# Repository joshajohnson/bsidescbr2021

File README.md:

# BSidesCBR2021
Slides and Design Files for BSides Canberra 2021

## Contents:
- `slides-ehd` slides for my "Electronic Hardware Design" talk.
- `pcb-ehd` design files for my "Electronic Hardware Design" talk.
    - `pcb-ehd/integrated-pcb` is the fully integrated bow tie.
    - `pcb-ehd/module-pcb` is the circular PCB using a Feather and microphone breakout.
    - `pcb-ehd/parts-lib` are custom footprints used in the above projects.
- `pcb-sao-magpie` design files for the Magpie SAO.

## PCB Design Files
**NOTE:** Both of the `pcb-ehd` projects have major issues with footprints and layout. **DO NOT manufacture these designs.** The Magpie SAO can however be manufactured if desired.

The `pcb-ehd` files require a recent KiCad Nightly build to open, whereas the SAO can be opened in KiCad 5.

In each of the project folders, you will find the below files:

- `proj.kicad_pro` is the overall KiCad project (`.pro` for V5).
- `proj.kicad_sch` is the schematic (`.sch` for V5).
- `proj.kicad_pcb` is the physical layout.
- `outputs/schematic.pdf` is a PDF of the schematic.
- `outputs/assembly.html` is a "Human Pick and Place" file which will help you hand assemble the board.
- `outputs/bom.csv` is the bill of materials required to populate the boards. I have not fully specified the resistors and capacitors for the integrated PCB.

## Resources:   
- [Digikey KiCad Series](https://www.youtube.com/watch?v=vaCVh2SAZY4)
- [KiCad PCB Design Walkthrough](https://www.youtube.com/watch?v=C7-8nUU6e3E)
- [PCB Design in Reverse](https://www.youtube.com/watch?v=CV68US8gZMk)
- [PCB Design Tutorial](https://alternatezone.com/electronics/files/-PCBDesignTutorialRevA.pdf)
- [Chris Gammell / Contextual Electronics](https://www.youtube.com/user/-contextualelectronic/videos)
- [100 Hardware Design Tips](https://www.youtube.com/watch?v=ZpMvKJzZk90&-list=PLXvLToQzgzddPKq_txEXNe0pxaSHqPtMO)
- [PCB Art](http://www.andrewsowa.com/blog/2017/3/19/creating-the-benchoff-nickel) 
- [Interactive HTML BOM](https://github.com/openscopeproject/InteractiveHtmlBom)

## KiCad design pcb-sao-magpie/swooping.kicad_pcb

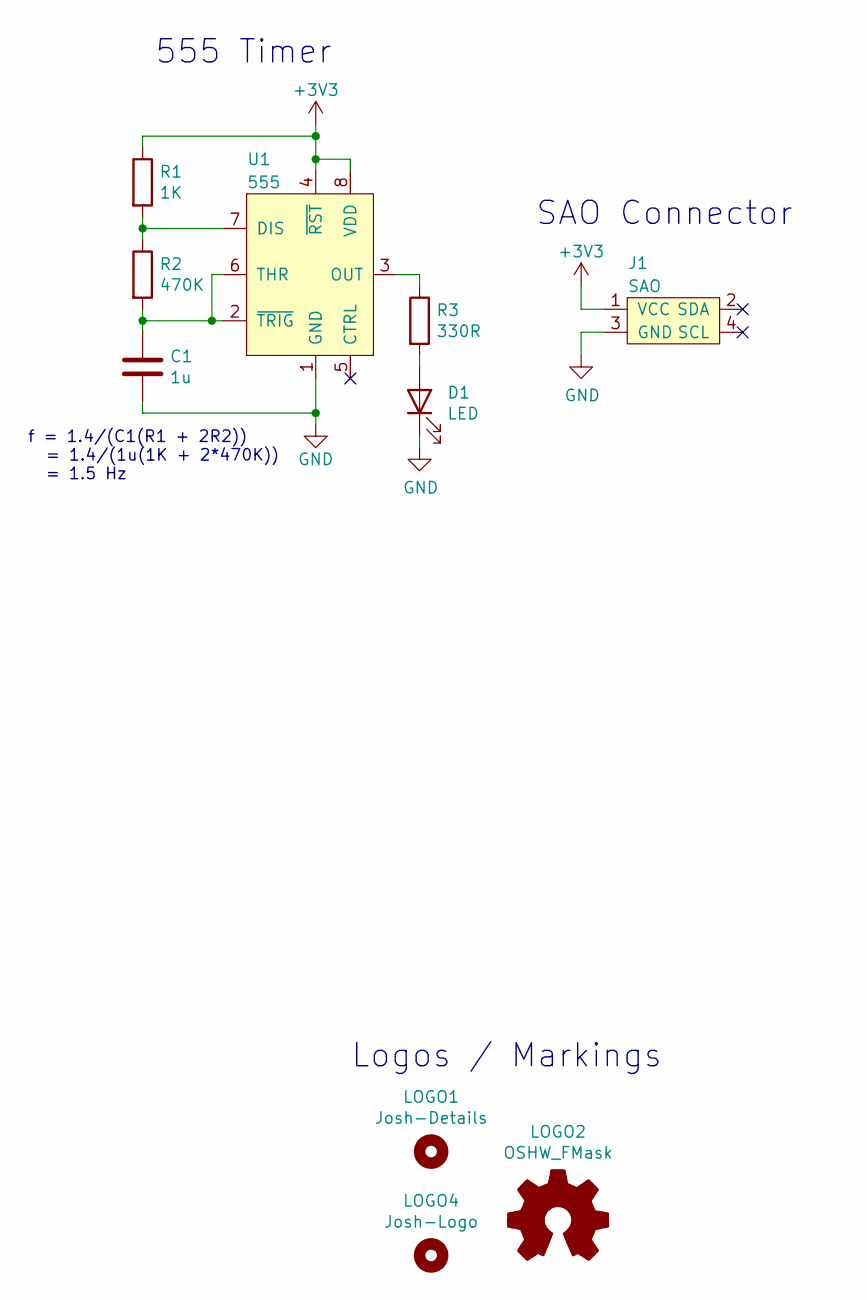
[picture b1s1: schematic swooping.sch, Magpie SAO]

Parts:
C1: 1u; C_1206_3216Metric_Pad1.42x1.75mm_HandSolder; MPN CL31B105KOFNNNE
D1: LED; LED_D5.0mm; MPN L513SRD-C
J1: SAO; PinHeader_2x02_P2.54mm_Vertical; MPN 10129382-904001BLF
LOGO1: Josh-Details; josh-details
LOGO2: OSHW_FMask; OSHW_Logo_3.6x3.6_F.Mask
LOGO4: Josh-Logo; josh-johnson-logo-8_6x1_5
R1: 1K; R_1206_3216Metric_Pad1.42x1.75mm_HandSolder; MPN RMCF1206JT1K00
R2: 470K; R_1206_3216Metric_Pad1.42x1.75mm_HandSolder; MPN RMCF1206JT470K
R3: 330R; R_1206_3216Metric_Pad1.42x1.75mm_HandSolder; MPN RMCF1206JT330R
U1: 555; SOIC-8_3.9x4.9mm_P1.27mm; MPN TLC555

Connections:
+3V3: J1.1 (VCC), R1.1, U1.4 (~RST), U1.8 (VDD)
GND: C1.2, D1.1 (K), J1.3 (GND), U1.1 (GND)
unnamed: C1.1, R2.2, U1.2 (~TRIG), U1.6 (THR)
unnamed: D1.2 (A), R3.2
unnamed: R1.2, R2.1, U1.7 (DIS)
unnamed: R3.1, U1.3 (OUT)

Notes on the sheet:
555 Timer
f = 1.4/(C1(R1 + 2R2)) = 1.4/(1u(1K + 2*470K)) = 1.5 Hz
SAO Connector
Logos / Markings

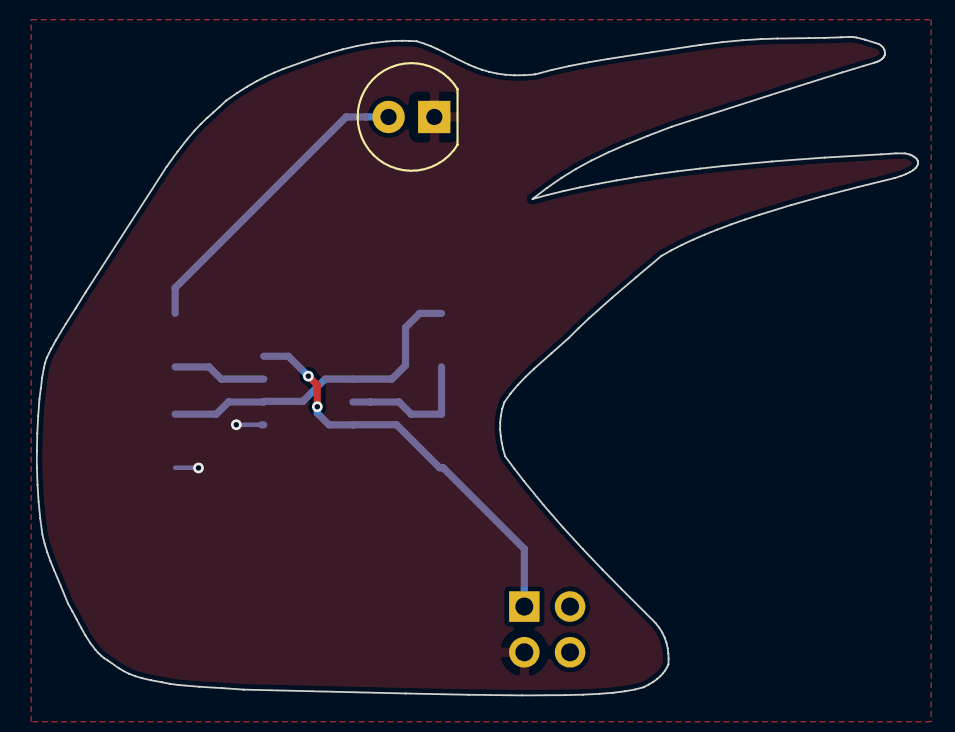
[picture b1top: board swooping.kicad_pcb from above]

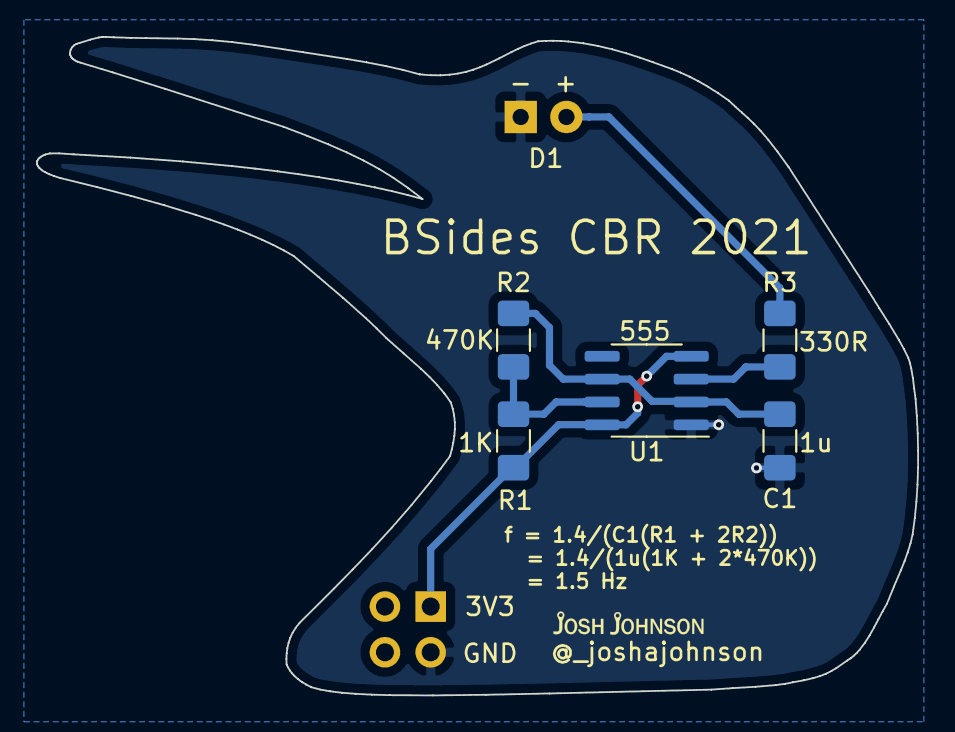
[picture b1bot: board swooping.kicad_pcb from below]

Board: 2 copper layers, 49.0 x 36.6 mm, 10 parts (8 on the bottom side), 6 nets.

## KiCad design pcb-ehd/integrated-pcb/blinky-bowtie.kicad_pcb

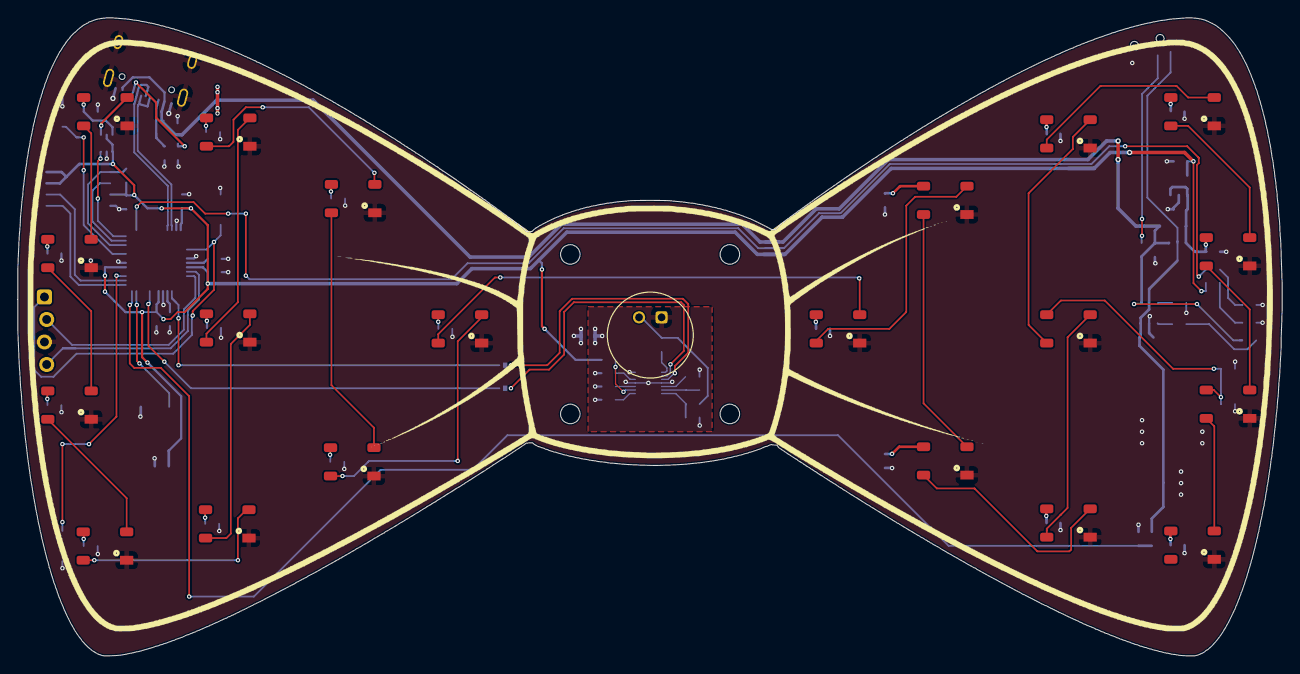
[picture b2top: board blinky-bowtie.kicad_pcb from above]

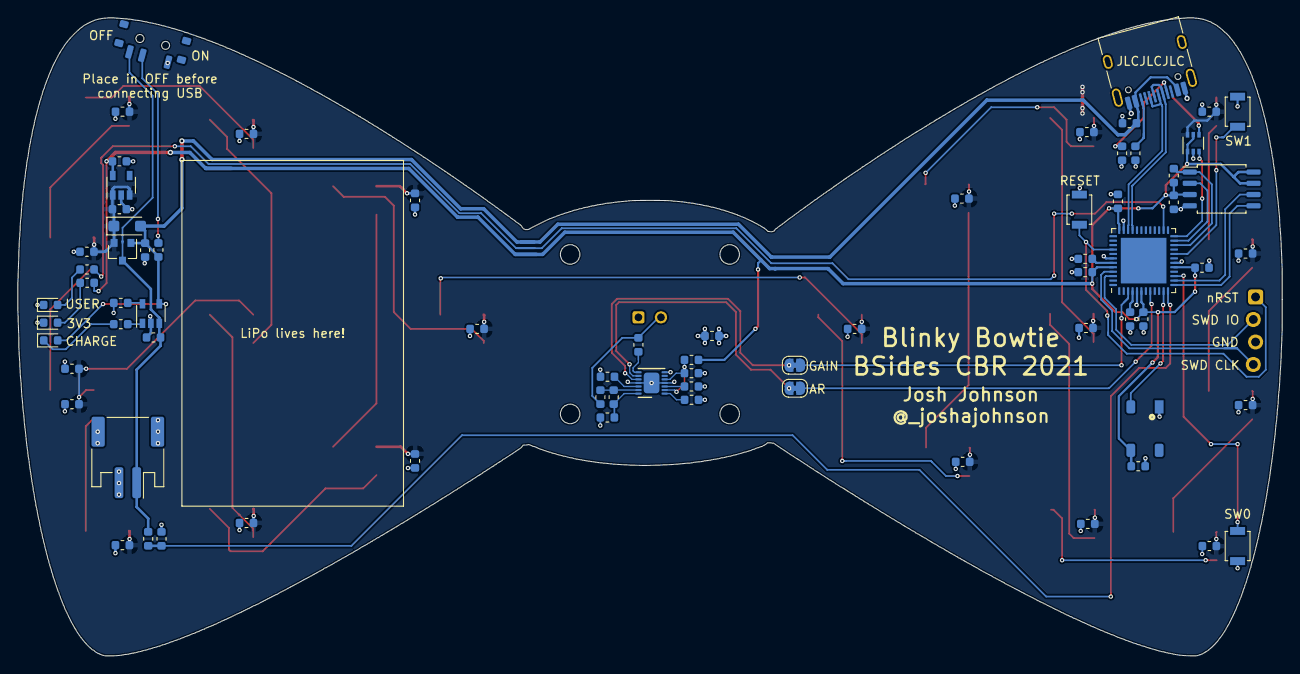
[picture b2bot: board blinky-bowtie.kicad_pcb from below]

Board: 2 copper layers, 142.7 x 72.0 mm, 101 parts (74 on the bottom side), 63 nets.

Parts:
C1: 4u7; C_0603_1608Metric
C2, C5, C7, C8, C9, C10, C12, C13, C14, C15, C16, C17, C18, C22, C23, C24, C25, C26, C27, C28, C29, C30, C31, C32, C33, C36: 100n; C_0603_1608Metric
C3, C4, C6: 10u; C_0603_1608Metric
C11, C19, C20, C21, C37: 1u; C_0603_1608Metric
C34: 470n; C_0603_1608Metric
C35: 2u2; C_0603_1608Metric
D1: RED; LED_0603_1608Metric
D2: ORG; LED_0603_1608Metric
D3, D6, D7, D8, D9, D10, D11, D12, D13, D14, D15, D16, D17, D18, D19, D20, D21, D22, D23, D24, D25: WS2812B; LED_WS2812B_PLCC4_5.0x5.0mm_P3.2mm
D4: PWR; LED_0603_1608Metric
D5: MBR120; D_SOD-123FL
FB1, FB2: 600R; R_0603_1608Metric
H1, H2, H3, H4: M2; MountingHole_2.2mm_M2_DIN965
J1: USB_C_Receptacle_USB2.0; USB_C_Receptacle_HRO_TYPE-C-31-M-12
J2: JST_PH; JST_PH_S2B-PH-SM4-TB_1x02-1MP_P2.00mm_Horizontal
J3: SWD; 4_PIN_THT_Staggered
JP1: GAIN; SolderJumper-2_P1.3mm_Bridged_RoundedPad1.0x1.5mm
JP2: AR; SolderJumper-2_P1.3mm_Bridged_RoundedPad1.0x1.5mm
LOGO1: F.Silk; bowtie-f-silk
LOGO2: Edge.Cuts; bowtie-edge-cuts
MK1: Mic; MIC_CMA-4544PF-W
Q1: DMP2045U; SOT-23
R1, R2, R7: 1K; R_0603_1608Metric
R3, R5: 5K1; R_0603_1608Metric
R4, R6, R8, R10: 100K; R_0603_1608Metric
R9, R13, R14: 10K; R_0603_1608Metric
R11: 150K; R_0603_1608Metric
R12: 2K2; R_0603_1608Metric
SW1, SW2, SW3: B3U; SW_SPST_B3U-1000P
SW4: SLIDE; SW_SPDT_PCM12
U1: MCP73831T-2; SOT-23-5
U2: ATSAMD21G18A-M; QFN-48-1EP_7x7mm_P0.5mm_EP5.15x5.15mm
U3: AP2112K-3.3; SOT-23-5
U4: MAX9814; DFN-14-1EP_3x3mm_P0.4mm_EP1.78x2.35mm
U5: W25Q32JVZPIQ; SOP-8_5.28x5.23mm_P1.27mm
U6: SN74LVC1T45DCK; SOT-363_SC-70-6

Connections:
+3V3: C2.1, C6.1, C11.1, C12.1, C13.1, C36.1, C37.1, D3.1 (VDD), FB1.1, R7.2, R13.1, U2.6 (VDDANA), U2.17 (VDDIO), U2.36 (VDDIO), U2.44 (VDDIN), U3.5 (VOUT), U5.3 (IO2), U5.7 (IO3), U5.8 (VCC), U6.1 (VCCA), U6.5 (DIR)
+5V: C1.1, D2.2 (A), D5.2 (A), J1.A4 (VBUS), J1.A9 (VBUS), J1.B4 (VBUS), J1.B9 (VBUS), Q1.1 (G), R4.1, R14.2, U1.4 (VDD)
+BATT: C4.1, J2.1, Q1.3 (D), R6.1, SW4.3 (C), U1.3 (VBAT)
/A0: JP1.1 (A), U2.3 (PA02)
/A2: JP2.1 (A), U2.8 (PB09)
/AR: JP2.2 (B), U4.9 (A/R)
/AREF: C20.1, U2.4 (PA03)
/D1: SW1.1, U2.15 (PA10)
/D5: U2.24 (PA15), U6.3 (A)
/D8_NEOPIX: D3.4 (DIN), U2.11 (PA06)
/D9: R6.2, R8.1, U2.12 (PA07)
/D13: R1.2, U2.26 (PA17)
/D+: J1.A6 (D+), J1.B6 (D+), U2.34 (PA25)
/D-: J1.A7 (D-), J1.B7 (D-), U2.33 (PA24)
/FLASH_CS: R13.2, U2.22 (PA13), U5.1 (~CS)
/FLASH_MISO: U2.23 (PA14), U5.2 (DO(IO1))
/FLASH_MOSI: U2.13 (PA08), U5.5 (DI(IO0))
/FLASH_SCK: U2.14 (PA09), U5.6 (CLK)
/GAIN: JP1.2 (B), U4.10 (GAIN)
/SCK: SW3.1, U2.20 (PB11)
/SWD_CLK: J3.4, U2.45 (PA30)
/SWD_IO: J3.2, U2.46 (PA31)
/nRST: J3.1, SW2.1, U2.40 (~RESET)
GND: C1.2, C2.2, C3.2, C4.2, C5.2, C6.2, C7.2, C8.2, C9.2, C10.2, C11.2, C12.2, C13.2, C14.2, C15.2, C16.2, C17.2, C18.2, C19.2, C20.2, C22.2, C23.2, C24.2, C25.2, C26.2, C29.2, C30.2, C31.2, C32.2, C33.2, C36.2, C37.2, D1.1 (K), D3.3 (VSS), D4.1 (K), D6.3 (VSS), D7.3 (VSS), D8.3 (VSS), D9.3 (VSS), D10.3 (VSS), D11.3 (VSS), D12.3 (VSS), D13.3 (VSS), D14.3 (VSS), D15.3 (VSS), D16.3 (VSS), D17.3 (VSS), D18.3 (VSS), D19.3 (VSS), D20.3 (VSS), D21.3 (VSS), D22.3 (VSS), D23.3 (VSS), D24.3 (VSS), D25.3 (VSS), FB2.2, J1.A1 (GND), J1.A12 (GND), J1.B1 (GND), J1.B12 (GND), J1.S1 (SHIELD), J2.2, J3.3, R3.1, R4.2, R5.2, R8.2, R9.2, SW1.2, SW2.2, SW3.2, SW4.1 (A), U1.2 (VSS), U2.5 (GNDANA), U2.18 (GND), U2.35 (GND), U2.42 (GND), U3.2 (GND), U5.4 (GND), U6.2 (GND)
GNDA: C21.2, C27.1, C34.2, C35.2, FB2.1, MK1.1 (-), R10.2, U4.4 (GND), U4.7 (GND), U4.11 (GND), U4.15 (GND)
unnamed: C19.1, U2.43 (VDDCORE)
unnamed: C21.1, FB1.2, U4.2 (~SHDN), U4.5 (VDD)
unnamed: C27.2, U4.1 (CT)
unnamed: C28.1, MK1.2 (+), R12.2
unnamed: C28.2, U4.8 (MICIN)
unnamed: C34.1, U4.12 (BIAS)
unnamed: C35.1, U4.3 (CG)
unnamed: D1.2 (A), R1.1
unnamed: D2.1 (K), R2.2
unnamed: D4.2 (A), R7.1
unnamed: D6.2 (DOUT), D7.4 (DIN)
unnamed: D6.4 (DIN), U6.4 (B)
unnamed: D7.2 (DOUT), D8.4 (DIN)
unnamed: D8.2 (DOUT), D9.4 (DIN)
unnamed: D10.2 (DOUT), D11.4 (DIN)
unnamed: D9.2 (DOUT), D10.4 (DIN)
unnamed: D11.2 (DOUT), D12.4 (DIN)
unnamed: D12.2 (DOUT), D13.4 (DIN)
unnamed: D13.2 (DOUT), D14.4 (DIN)
unnamed: D14.2 (DOUT), D15.4 (DIN)
unnamed: D15.2 (DOUT), D16.4 (DIN)
unnamed: D16.2 (DOUT), D17.4 (DIN)
unnamed: D17.2 (DOUT), D18.4 (DIN)
unnamed: D18.2 (DOUT), D19.4 (DIN)
unnamed: D19.2 (DOUT), D20.4 (DIN)
unnamed: D20.2 (DOUT), D21.4 (DIN)
unnamed: D21.2 (DOUT), D22.4 (DIN)
unnamed: D22.2 (DOUT), D23.4 (DIN)
unnamed: D23.2 (DOUT), D24.4 (DIN)
unnamed: D24.2 (DOUT), D25.4 (DIN)
unnamed: J1.A5 (CC1), R5.1
unnamed: J1.B5 (CC2), R3.2
unnamed: R2.1, U1.1 (STAT)
unnamed: R9.1, U1.5 (PROG)
unnamed: R10.1, R11.1, U4.14 (TH)
unnamed: R11.2, R12.1, U4.13 (MICBIAS)
unnamed: R14.1, SW4.2 (B)
VCC: C3.1, C5.1, C7.1, C8.1, C9.1, C10.1, C14.1, C15.1, C16.1, C17.1, C18.1, C22.1, C23.1, C24.1, C25.1, C26.1, C29.1, C30.1, C31.1, C32.1, C33.1, D5.1 (K), D6.1 (VDD), D7.1 (VDD), D8.1 (VDD), D9.1 (VDD), D10.1 (VDD), D11.1 (VDD), D12.1 (VDD), D13.1 (VDD), D14.1 (VDD), D15.1 (VDD), D16.1 (VDD), D17.1 (VDD), D18.1 (VDD), D19.1 (VDD), D20.1 (VDD), D21.1 (VDD), D22.1 (VDD), D23.1 (VDD), D24.1 (VDD), D25.1 (VDD), Q1.2 (S), U3.1 (VIN), U3.3 (EN), U6.6 (VCCB)

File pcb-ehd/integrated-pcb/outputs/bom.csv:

Reference, Quantity, Value, Footprint, LCSC, MPN, Manufacturer
C1 ,1,4u7,Capacitor_SMD:C_0603_1608Metric,,,
C11 C19 C20 C21 C37 ,5,1u,Capacitor_SMD:C_0603_1608Metric,,,
C2 C12 C13 C27 C28 C36 C5 C7 C8 C9 C10 C14 C15 C16 C17 C18 C22 C23 C24 C25 C26 C29 C30 C31 C32 C33 ,26,100n,Capacitor_SMD:C_0603_1608Metric,,,
C3 C4 C6 ,3,10u,Capacitor_SMD:C_0603_1608Metric,,,
C34 ,1,470n,Capacitor_SMD:C_0603_1608Metric,,,
C35 ,1,2u2,Capacitor_SMD:C_0603_1608Metric,,,
D1 ,1,RED,LED_SMD:LED_0603_1608Metric,C2286,KT-0603R,Hubei KENTO Elec
D2 ,1,ORG,LED_SMD:LED_0603_1608Metric,C375450,E6C0603SEAC1UDA,EKINGLUX
D3 D6 D7 D8 D9 D10 D11 D12 D13 D14 D15 D16 D17 D18 D19 D20 D21 D22 D23 D24 D25 ,21,WS2812B,ehd:LED_WS2812B_PLCC4_5.0x5.0mm_P3.2mm,C114586,WS2812B-B,Worldsemi
D4 ,1,PWR,LED_SMD:LED_0603_1608Metric,C72041,19-217/BHC-ZL1M2RY/3T,Everlight Elec
D5 ,1,MBR120,ehd:D_SOD-123FL,C236132,MBR120ESFT1G,ON Semiconductor
FB1 FB2 ,2,600R,Resistor_SMD:R_0603_1608Metric,C76884,BLM15AG601SN1D,Murata Electronics
J1 ,1,USB_C_Receptacle_USB2.0,ehd:USB_C_Receptacle_HRO_TYPE-C-31-M-12,C165948,TYPE-C-31-M-12,Korean Hroparts Elec
J2 ,1,JST_PH,ehd:JST_PH_S2B-PH-SM4-TB_1x02-1MP_P2.00mm_Horizontal,C47647,S2B-PH-SM4-TB(LF)(SN),JST
MK1 ,1,Mic,ehd:MIC_CMA-4544PF-W,,MIC_CMA-4544PF-W,CUI Devices
Q1 ,1,DMP2045U,Package_TO_SOT_SMD:SOT-23,C459541,DMP2045U-7,Diodes Incorporated
R1 R2 R7 ,3,1K,Resistor_SMD:R_0603_1608Metric,,,
R11 ,1,150K,Resistor_SMD:R_0603_1608Metric,,,
R12 ,1,2K2,Resistor_SMD:R_0603_1608Metric,,,
R3 R5 ,2,5K1,Resistor_SMD:R_0603_1608Metric,,,
R4 R6 R8 R10 ,4,100K,Resistor_SMD:R_0603_1608Metric,,,
R9 R13 R14 ,3,10K,Resistor_SMD:R_0603_1608Metric,,,
SW1 SW2 SW3 ,3,B3U,Button_Switch_SMD:SW_SPST_B3U-1000P,C231329,B3U-1000P,Omron Electronics
SW4 ,1,SLIDE,ehd:SW_SPDT_PCM12,C221841,PCM12SMTR,C&K
U1 ,1,MCP73831T-2,Package_TO_SOT_SMD:SOT-23-5,C424093,MCP73831T-2ACI/OT,Microchip Technology
U2 ,1,ATSAMD21G18A-M,Package_DFN_QFN:QFN-48-1EP_7x7mm_P0.5mm_EP5.15x5.15mm,C1338342,ATSAMD21G18A-MF,Microchip Tech
U3 ,1,AP2112K-3.3,Package_TO_SOT_SMD:SOT-23-5,C51118 ,AP2112K-3.3TRG1,Diodes Incorporated
U4 ,1,MAX9814,Package_DFN_QFN:DFN-14-1EP_3x3mm_P0.4mm_EP1.78x2.35mm,C41714,MAX9814ETD+T,Maxim
U5 ,1,GD25Q16CSIGR,Package_SO:SOP-8_5.28x5.23mm_P1.27mm,C395505,GD25Q16CSIGR,Gigadevices
U6 ,1,SN74LVC1T45DCK,Package_TO_SOT_SMD:SOT-363_SC-70-6,C80768,SN74LVC1T45DCKT,Texas Instruments

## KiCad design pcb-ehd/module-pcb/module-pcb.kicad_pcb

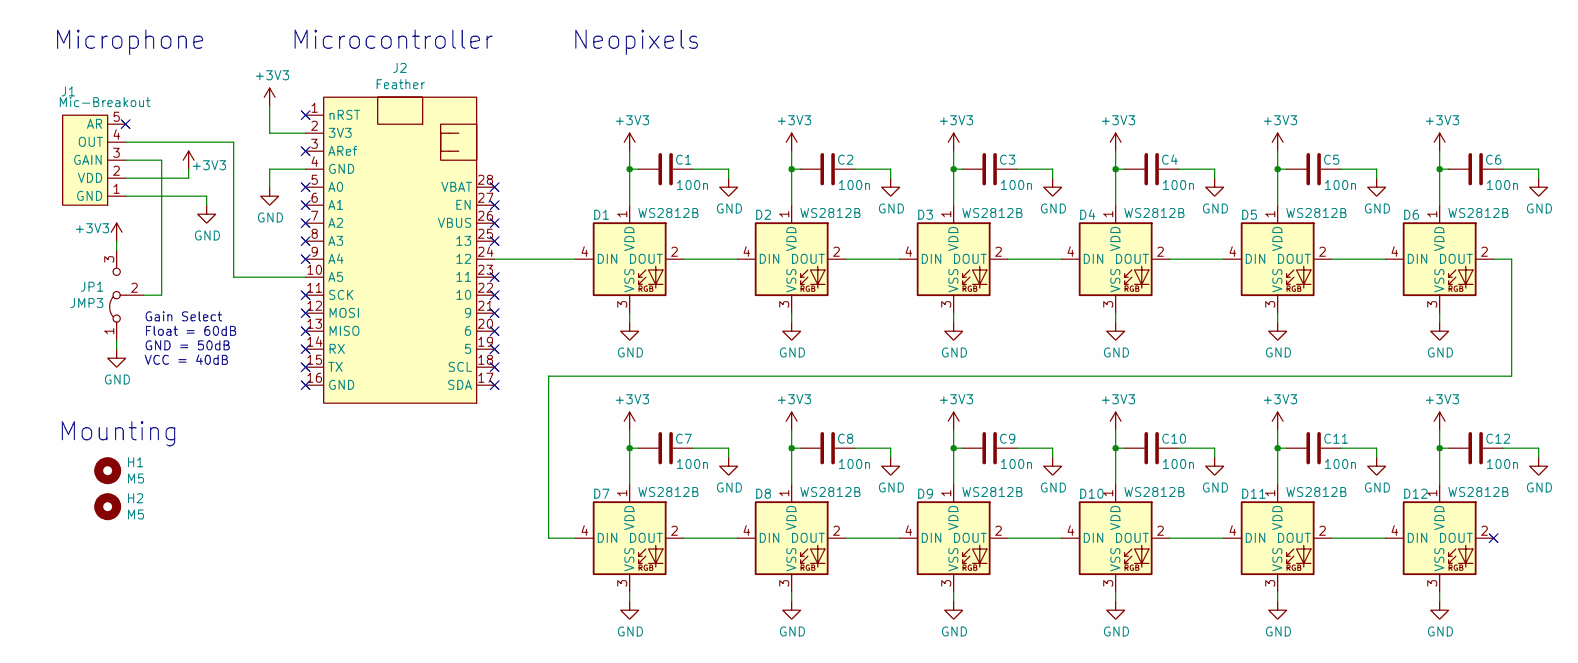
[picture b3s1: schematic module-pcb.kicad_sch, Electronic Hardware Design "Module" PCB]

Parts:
C1, C2, C3, C4, C5, C6, C7, C8, C9, C10, C11, C12: 100n; C_0805_2012Metric; MPN 0805ZD104KAT2A; Mouser PN 581-0805ZD104KAT2A
D1, D2, D3, D4, D5, D6, D7, D8, D9, D10, D11, D12: WS2812B; LED_WS2812B_PLCC4_5.0x5.0mm_P3.2mm; MPN COM-16346; Mouser PN 474-COM-16346
H1, H2: M5; MountingHole_5mm
J1: Mic-Breakout; MPN 1713; Mouser PN 485-1713
J2: Feather; featherwing; MPN 3403; Mouser PN 485-3403
JP1: JMP3; SolderJumper-3_P1.3mm_Bridged12_RoundedPad1.0x1.5mm

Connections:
+3V3: C1.1, C2.1, C3.1, C4.1, C5.1, C6.1, C7.1, C8.1, C9.1, C10.1, C11.1, C12.1, D1.1 (VDD), D2.1 (VDD), D3.1 (VDD), D4.1 (VDD), D5.1 (VDD), D6.1 (VDD), D7.1 (VDD), D8.1 (VDD), D9.1 (VDD), D10.1 (VDD), D11.1 (VDD), D12.1 (VDD), J1.2 (VDD), J2.2 (3V3), JP1.3 (B)
GND: C1.2, C2.2, C3.2, C4.2, C5.2, C6.2, C7.2, C8.2, C9.2, C10.2, C11.2, C12.2, D1.3 (VSS), D2.3 (VSS), D3.3 (VSS), D4.3 (VSS), D5.3 (VSS), D6.3 (VSS), D7.3 (VSS), D8.3 (VSS), D9.3 (VSS), D10.3 (VSS), D11.3 (VSS), D12.3 (VSS), J1.1 (GND), J2.4 (GND), JP1.1 (A)
unnamed: D1.2 (DOUT), D2.4 (DIN)
unnamed: D1.4 (DIN), J2.24 (12)
unnamed: D2.2 (DOUT), D3.4 (DIN)
unnamed: D3.2 (DOUT), D4.4 (DIN)
unnamed: D4.2 (DOUT), D5.4 (DIN)
unnamed: D5.2 (DOUT), D6.4 (DIN)
unnamed: D6.2 (DOUT), D7.4 (DIN)
unnamed: D7.2 (DOUT), D8.4 (DIN)
unnamed: D8.2 (DOUT), D9.4 (DIN)
unnamed: D10.2 (DOUT), D11.4 (DIN)
unnamed: D9.2 (DOUT), D10.4 (DIN)
unnamed: D11.2 (DOUT), D12.4 (DIN)
unnamed: J1.3 (GAIN), JP1.2 (C)
unnamed: J1.4 (OUT), J2.10 (A5)

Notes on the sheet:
Gain Select Float = 60dB GND = 50dB VCC = 40dB
Mounting
Microphone
Microcontroller
Neopixels

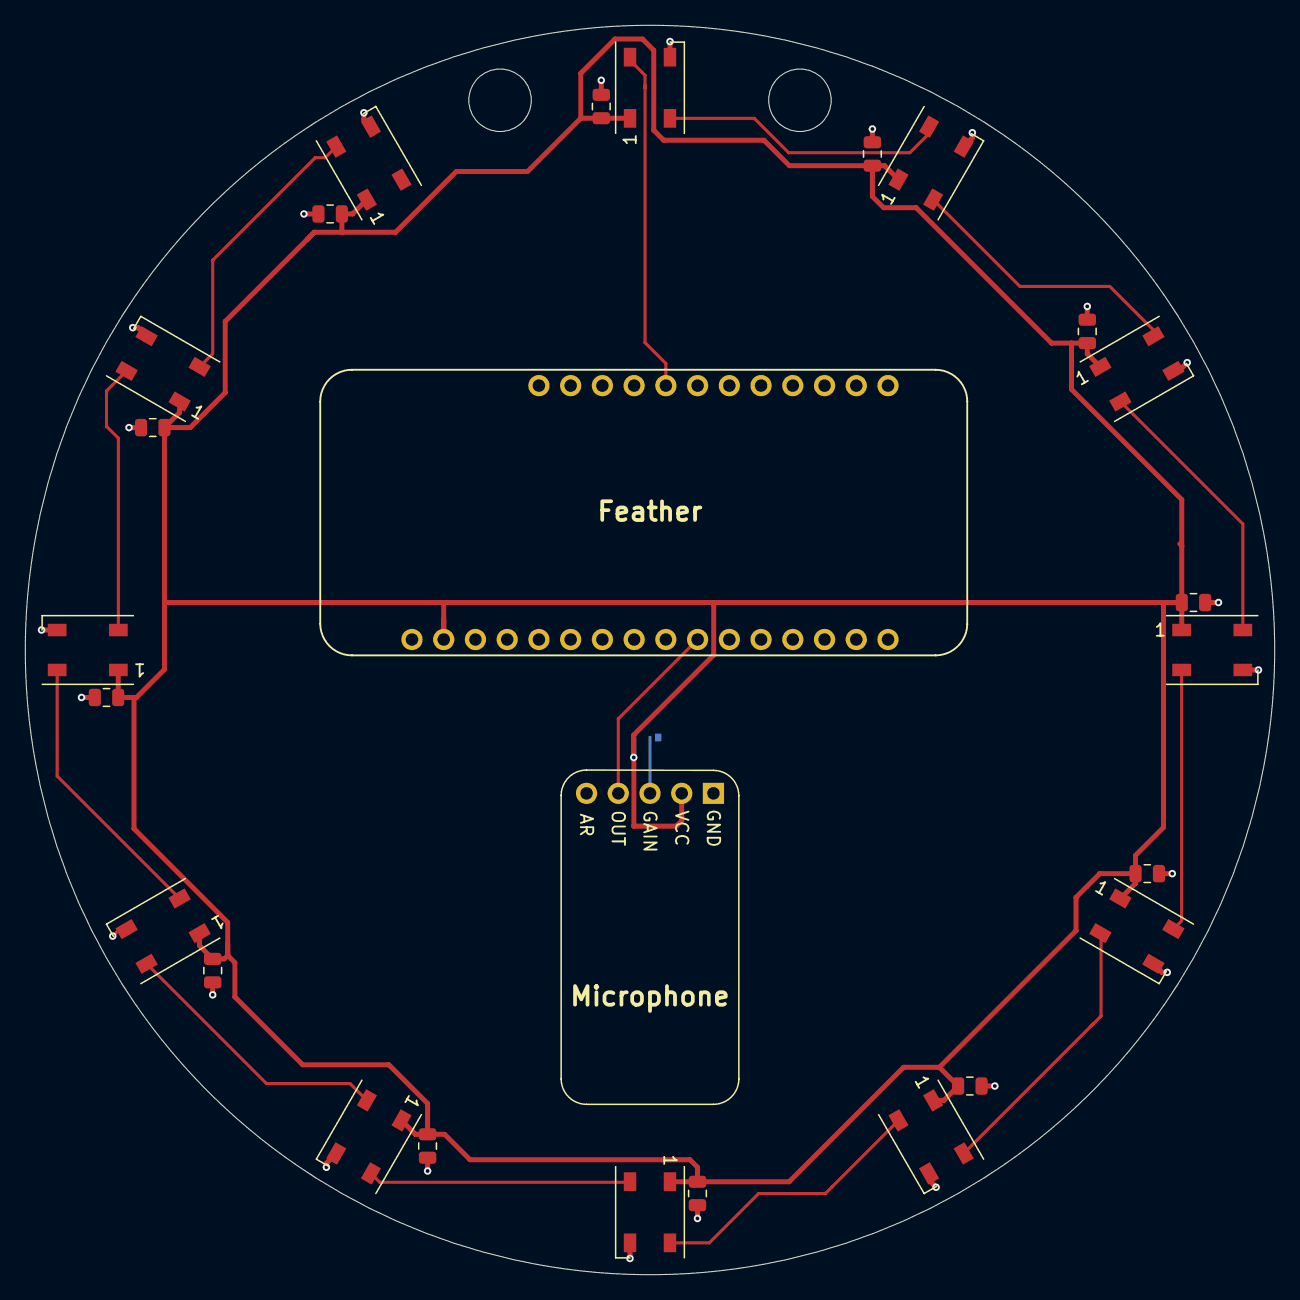
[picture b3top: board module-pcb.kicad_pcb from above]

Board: 2 copper layers, 100.0 x 100.0 mm, 29 parts (1 on the bottom side), 16 nets.

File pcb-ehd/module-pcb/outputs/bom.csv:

Reference, Quantity, Value, Footprint, MPN, Manufacturer, Mouser PN
C1 C2 C3 C4 C5 C6 C7 C8 C9 C10 C11 C12 ,12,100n,Capacitor_SMD:C_0805_2012Metric,0805ZD104KAT2A,AVX,581-0805ZD104KAT2A
D1 D2 D3 D4 D5 D6 D7 D8 D9 D10 D11 D12 ,12,WS2812B,LED_SMD:LED_WS2812B_PLCC4_5.0x5.0mm_P3.2mm,COM-16346 ,Sparkfun,474-COM-16346 
J1 ,1,Mic-Breakout,ehd:Mic-Breakout,1713,Adafruit,485-1713
J2 ,1,Feather,ehd:featherwing,3403,Adafruit,485-3403

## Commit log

2021-01-24 initial / generic pcb content first pass
2021-02-20 add kicad to gitigonre
2021-02-20 module PCB first pass
2021-02-21 first pass bow tie schematic + all footprints
2021-02-21 remove cached files
2021-02-22 bow tie graphics done
2021-02-23 rough placement of all but analog
2021-02-24 layout passes DRC
2021-03-08 first half slides update
2021-03-08 updates with ordering
2021-04-02 cleanup kicad files
2021-04-03 first pass slides done
2021-04-05 review done
2021-04-06 slides done, ship it!
2021-04-06 update image to be easier to read
2021-04-06 improve ibom screnshot
2021-04-08 add links
2021-04-08 formatting
2021-04-09 update final side
